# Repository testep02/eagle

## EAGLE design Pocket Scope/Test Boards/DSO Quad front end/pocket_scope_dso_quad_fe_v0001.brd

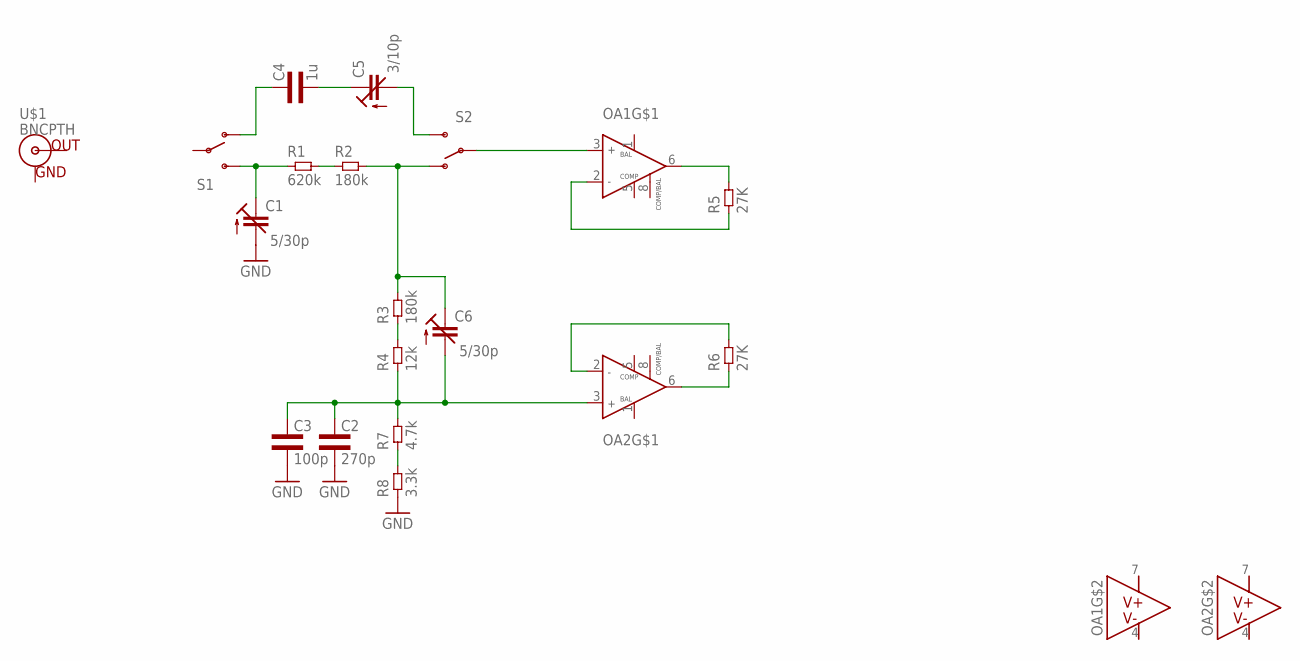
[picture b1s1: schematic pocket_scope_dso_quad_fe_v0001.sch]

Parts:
C1, C6: 5/30p; CTRIM3018_11
C2: 270p; 0603L3
C3: 100p; 0603L3
C4: 1u; 0603L3
C5: 3/10p; CTRIM3018_11
OA1, OA2: NE5534SOIC8; SOIC-8
R1: 620k; 0603L3
R2, R3: 180k; 0603L3
R4: 12k; 0603L3
R5, R6: 27K; 0603L3
R7: 4.7k; 0603L3
R8: 3.3k; 0603L3
S1, S2: SPARKFUN-ELECTROMECHANICAL_SWITCH-SPDTPTH_LOCK; SPARKFUN-ELECTROMECHANICAL_SWITCH-SPDT_LOCK.007S
U$1: BNCPTH; BNC

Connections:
GND: C1.- (A), C2.P$2 (2), C3.P$2 (2), R8.P$1 (1)
unnamed: C1.+ (E), R1.P$1 (1), S1.3 (S)
unnamed: R1.P$2 (2), R2.P$1 (1)
unnamed: C6.+ (E), R2.P$2 (2), R3.P$2 (2), S2.1 (O)
unnamed: OA1.3 (IN+), S2.2
unnamed: R3.P$1 (1), R4.P$2 (2)
unnamed: C2.P$1 (1), C3.P$1 (1), C6.- (A), OA2.3 (IN+), R4.P$1 (1), R7.P$2 (2)
unnamed: OA1.2 (IN-), R5.P$1 (1)
unnamed: OA2.2 (IN-), R6.P$2 (2)
unnamed: OA2.6 (OUT), R6.P$1 (1)
unnamed: OA1.6 (OUT), R5.P$2 (2)
unnamed: R7.P$1 (1), R8.P$2 (2)
unnamed: C5.- (A), S2.3 (S)
unnamed: C4.P$1 (1), S1.1 (O)
unnamed: C4.P$2 (2), C5.+ (E)
V+: OA1.7 (V+), OA2.7 (V+)
V-: OA1.4 (V-), OA2.4 (V-)

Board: 2 copper layers, 19 parts (0 on the bottom side), 17 nets, no tracks yet.

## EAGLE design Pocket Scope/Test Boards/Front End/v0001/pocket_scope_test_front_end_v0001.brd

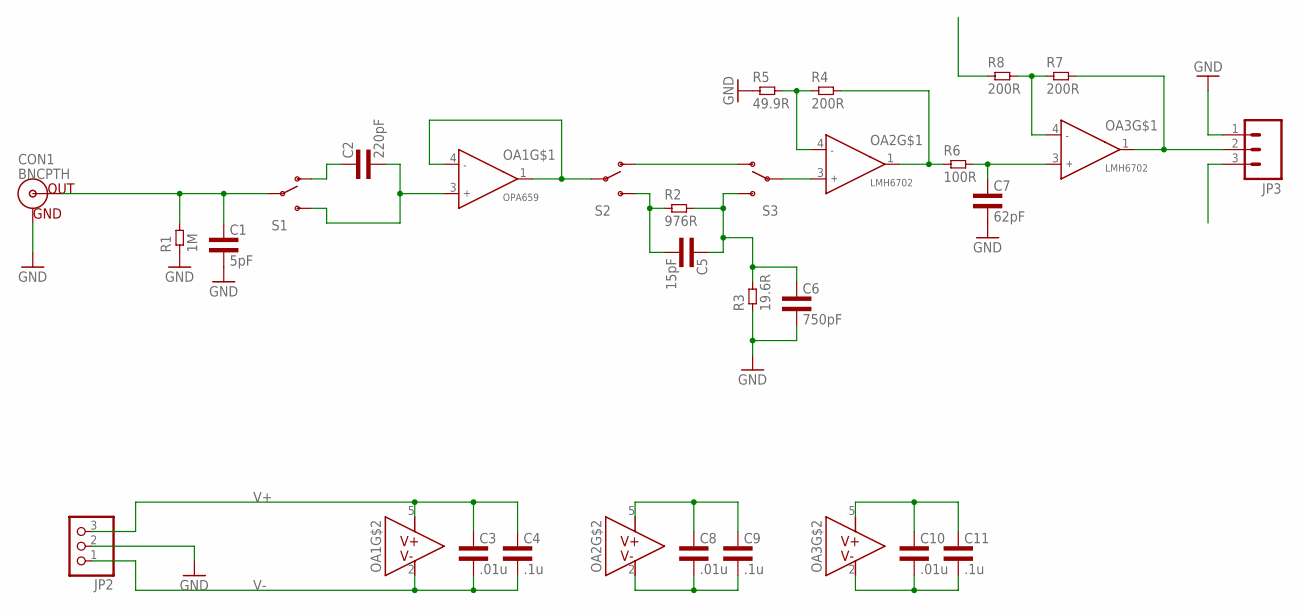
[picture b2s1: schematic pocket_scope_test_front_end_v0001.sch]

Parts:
C1: 5pF; 0805L3
C2: 220pF; 0805L3
C3, C8, C10: .01u; 0805L3
C4, C9, C11: .1u; 0805L3
C5: 15pF; 0805L3
C6: 750pF; 0805L3
C7: 62pF; 0805L3
CON1: BNCPTH; BNC
JP2: PINHD-1X3; 1X03
JP3: M03LOCK; 1X03_LOCK
OA1: OPA659; R-PDSO-G5
OA2, OA3: LMH6702; R-PDSO-G5
R1: 1M; 0805L3
R2: 976R; 0805L3
R3: 19.6R; 0805L3
R4, R7, R8: 200R; 0805L3
R5: 49.9R; 0805L3
R6: 100R; 0805L3
S1, S2, S3: SPARKFUN-ELECTROMECHANICAL_SWITCH-SPDTPTH_LOCK; SPARKFUN-ELECTROMECHANICAL_SWITCH-SPDT_LOCK.007S

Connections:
GND: C1.2, C6.2, C7.2, CON1.GND, JP2.2, JP3.1, R1.1, R3.1, R5.1
unnamed: C2.2, OA1.3 (INA+), S1.3 (S)
unnamed: C2.1, S1.1 (O)
unnamed: OA1.1 (OUTA), OA1.4 (INA-), S2.2
unnamed: C1.1, CON1.S (OUT), R1.2, S1.2
unnamed: C5.2, R2.1, S2.3 (S)
unnamed: C5.1, C6.1, R2.2, R3.2, S3.3 (S)
unnamed: S2.1 (O), S3.1 (O)
unnamed: OA2.3 (INA+), S3.2
unnamed: OA2.4 (INA-), R4.1, R5.2
unnamed: OA2.1 (OUTA), R4.2, R6.1
unnamed: C7.1, OA3.3 (INA+), R6.2
unnamed: JP3.2, OA3.1 (OUTA), R7.2
unnamed: OA3.4 (INA-), R7.1, R8.2
V+: C3.1, C4.1, C8.1, C9.1, C10.1, C11.1, JP2.3, OA1.5 (V+), OA2.5 (V+), OA3.5 (V+)
V-: C3.2, C4.2, C8.2, C9.2, C10.2, C11.2, JP2.1, OA1.2 (V-), OA2.2 (V-), OA3.2 (V-)
V_OS: JP3.3, R8.1

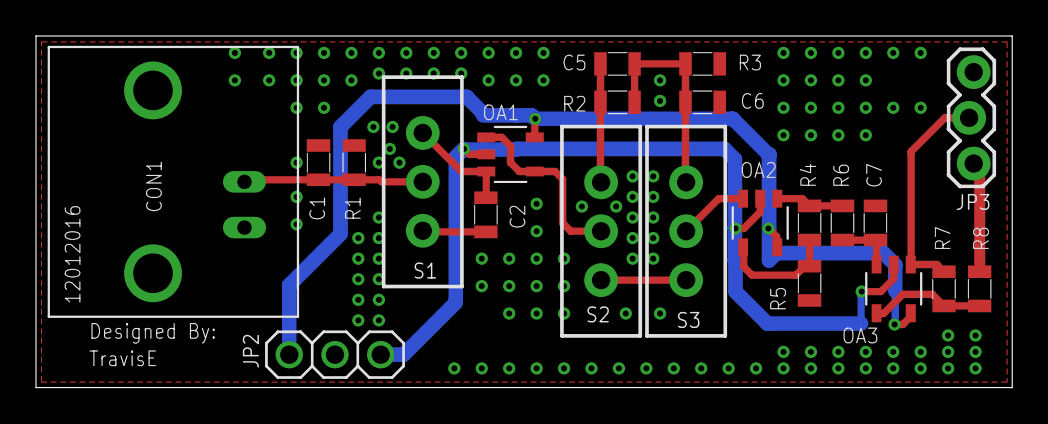
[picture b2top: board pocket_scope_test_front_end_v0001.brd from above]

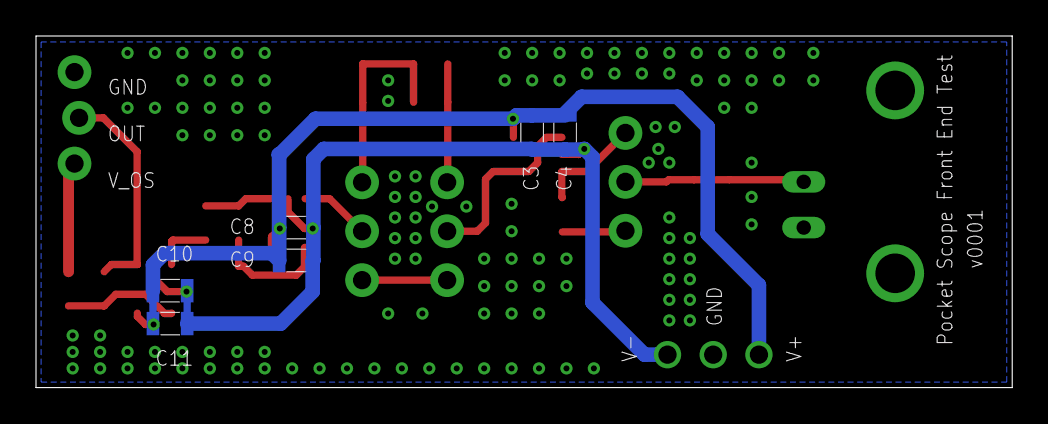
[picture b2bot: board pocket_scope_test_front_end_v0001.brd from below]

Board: 2 copper layers, 54.2 x 19.5 mm, 28 parts (6 on the bottom side), 17 nets.

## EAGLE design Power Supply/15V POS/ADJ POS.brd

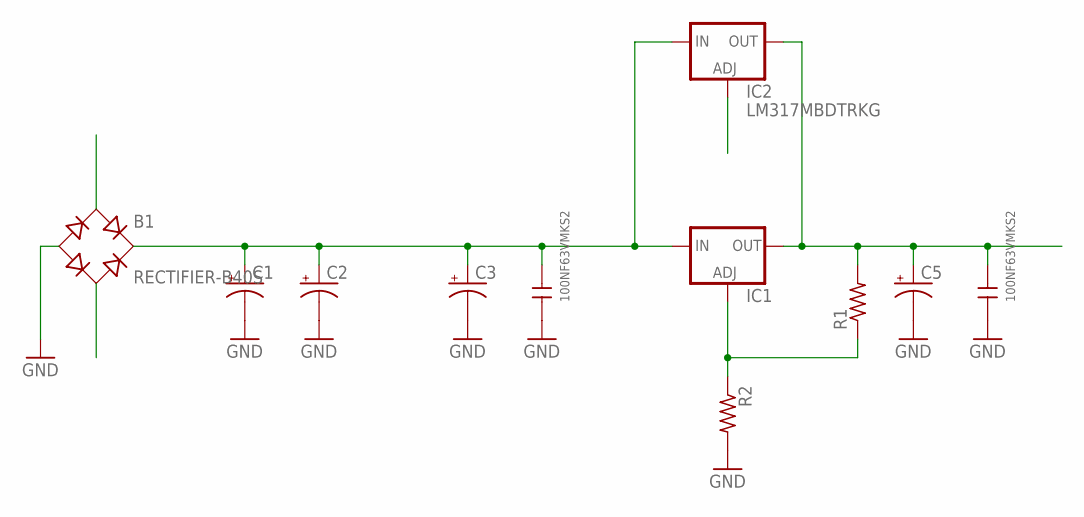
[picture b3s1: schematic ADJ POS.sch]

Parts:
B1: RECTIFIER-B40S; B40S
C1, C2: CPOL-USE7.5-16; E7,5-16
C3, C5: CPOL-USE2-5; E2-5
C4, C6: 100NF63VMKS2; 2,5X6,5RM5,0
IC1: LM317TS; 317TS
IC2: LM317MBDTRKG; DPACK
R1, R2: R-US_0309/12; 0309/12

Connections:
AC_1: B1.AC1
AC_2: B1.AC2
ADJ: IC1.1 (ADJ), IC2.1 (ADJ), R1.1, R2.1
GND: B1.-, C1.-, C2.-, C3.-, C4.1, C5.-, C6.1, R2.2
IN: B1.+, C1.+, C2.+, C3.+, C4.2, IC1.3 (IN), IC2.3 (IN)
OUT: C5.+, C6.2, IC1.2 (OUT), IC2.4 (OUT), R1.2

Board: 2 copper layers, 11 parts (0 on the bottom side), 4 nets, no tracks yet.

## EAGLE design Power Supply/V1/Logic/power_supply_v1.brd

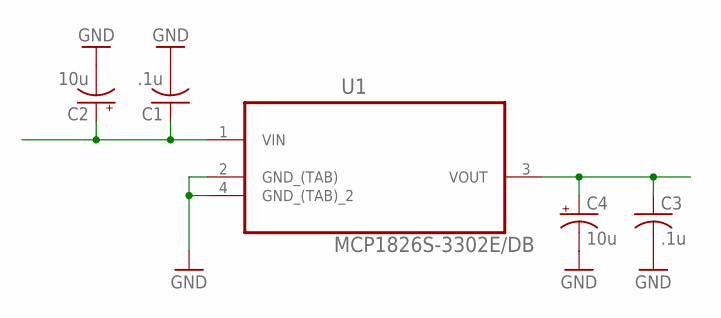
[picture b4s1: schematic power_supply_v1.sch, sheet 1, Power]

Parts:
C1, C3: .1u; C0603
C2, C4: 10u; D/7343-31W
U1: MCP1826S-3302E/DB; SOT230P700X180-4N

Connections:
3V3: C3.1, C4.+, U1.3 (VOUT)
GND: C1.2, C2.-, C3.2, C4.-, U1.2 (GND_(TAB)), U1.4 (GND_(TAB)_2)
unnamed: C1.1, C2.+, U1.1 (VIN)

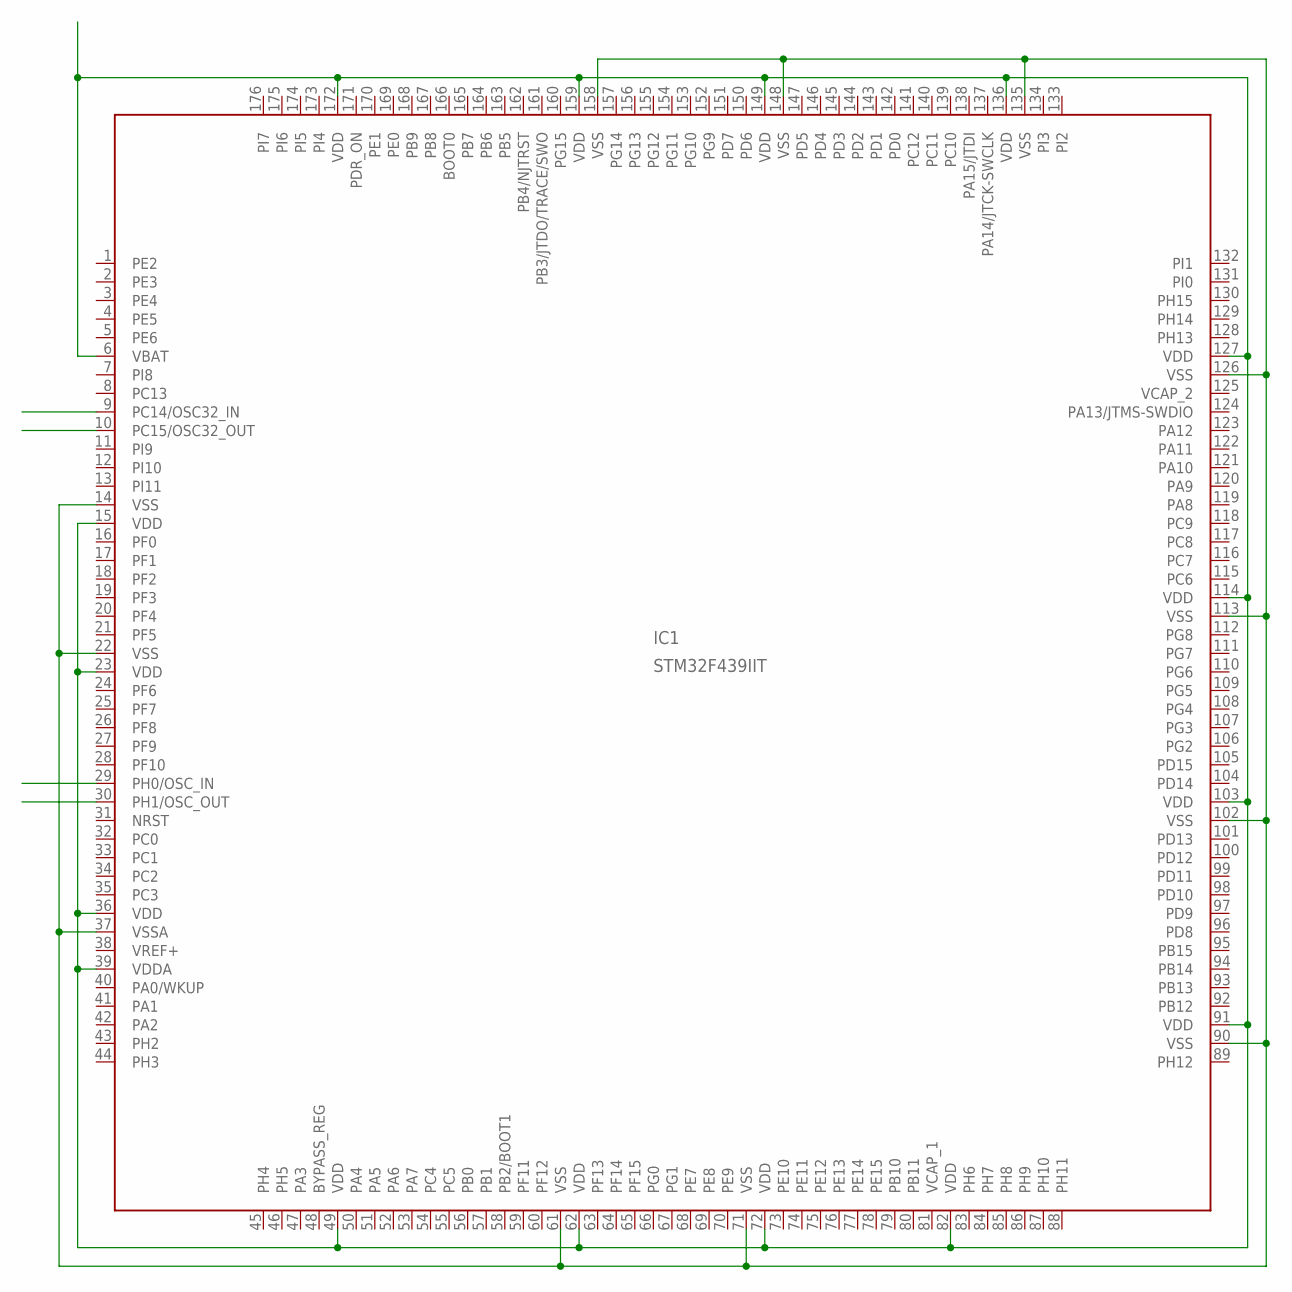
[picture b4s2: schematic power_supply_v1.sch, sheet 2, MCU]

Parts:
IC1: STM32F439IIT; LQFP-176

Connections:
unnamed: IC1.6 (VBAT), IC1.15 (VDD), IC1.23 (VDD), IC1.36 (VDD), IC1.39 (VDDA), IC1.49 (VDD), IC1.62 (VDD), IC1.72 (VDD), IC1.82 (VDD), IC1.91 (VDD), IC1.103 (VDD), IC1.114 (VDD), IC1.127 (VDD), IC1.136 (VDD), IC1.149 (VDD), IC1.159 (VDD), IC1.172 (VDD)
unnamed: IC1.14 (VSS), IC1.22 (VSS), IC1.37 (VSSA), IC1.61 (VSS), IC1.71 (VSS), IC1.90 (VSS), IC1.102 (VSS), IC1.113 (VSS), IC1.126 (VSS), IC1.135 (VSS), IC1.148 (VSS), IC1.158 (VSS)
PDR_ON: IC1.171 (PDR_ON)
VCAP_1: IC1.81 (VCAP_1)
VCAP_2: IC1.125 (VCAP_2)
VREF+: IC1.38 (VREF+)

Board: 2 copper layers, 6 parts (0 on the bottom side), 5 nets, no tracks yet.

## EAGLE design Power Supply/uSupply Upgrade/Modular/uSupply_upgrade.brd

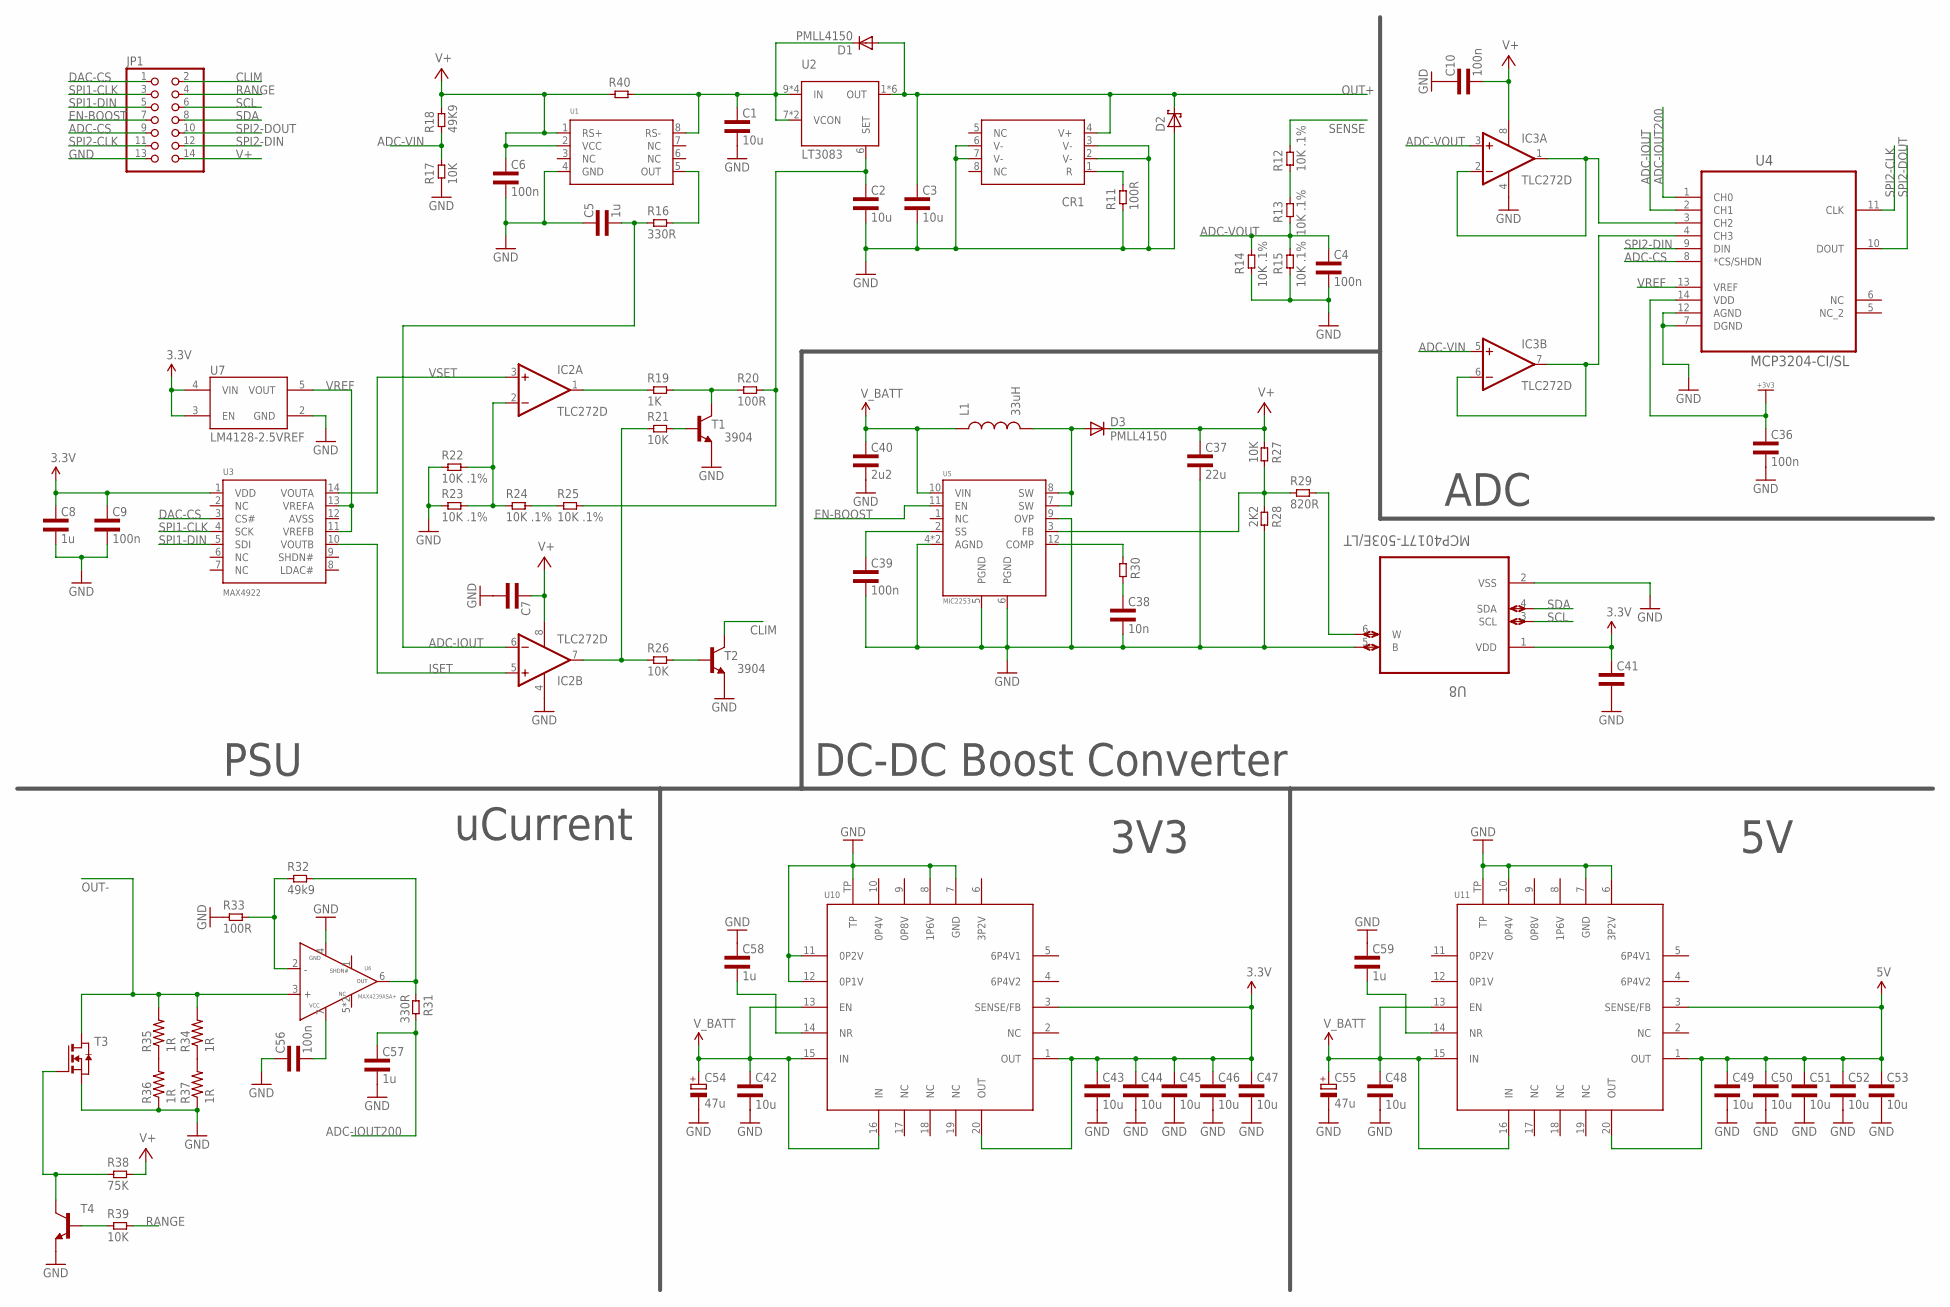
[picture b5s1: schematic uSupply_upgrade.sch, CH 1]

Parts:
C1, C2, C3, C42, C43, C44, C45, C46, C47, C48, C49, C50, C51, C52, C53: 10u; 0805L3
C4, C6, C9, C10, C36, C39, C56: 100n; 0603L3
C5, C8, C57, C58, C59: 1u; 0603L3
C7, C41: CAP0603L3; 0603L3
C37: 22u; 1206L3
C38: 10n; 0603L3
C40: 2u2; 0603L3
C54, C55: 47u; CT7343
CR1: LM334; R-PDSO-G8
D1, D3: PMLL4150; SOD80C
D2: SCHOTTKY-DIODESMD; SMB
IC2, IC3: TLC272D; SO08
JP1: PINHD-2X7; 2X07
L1: 33uH; SRN6045
R11, R20, R33: 100R; 0603L3
R12, R13, R14, R15, R22, R23, R24, R25: 10K .1%; 0603L3
R16, R31: 330R; 0603L3
R17, R21, R26, R27, R39: 10K; 0603L3
R18: 49K9; 0603L3
R19: 1K; 0603L3
R28: 2K2; 0603L3
R29: 820R; 0603L3
R30: RES0603L3; 0603L3
R32: 49k9; 0603L3
R34, R35, R36, R37: 1R; R2512
R38: 75K; 0603L3
R40: RES4527L3; 4527L3
T1, T2: 3904; SOT23-BEC
T3: NMOSSOT23; SOT-23
T4: MMBT3904LT1-NPN-SOT23-BEC; SOT23-BEC
U1: MAX4080; UMAX
U2: LT3083; DFN4X4
U3: MCP4922; TSSOP-14
U4: MCP3204-CI/SL; SOIC127P600X175-14N
U5: MIC2253; MLF3X3
U6: MAX4239; SOIC-8
U7: LM4128-2.5VREF; SOT23-5
U8: MCP4017T-503E/LT; SOT65P210X110-6N
U10, U11: POWER-SUPPLY_POS_V1_TI_LDO_TPS7A4700; POWER-SUPPLY_POS_V1_TI_LDO_VQFN-20

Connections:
3.3V: C8.P$1 (1), C9.P$1 (1), C41.P$1 (1), C43.1, C44.1, C45.1, C46.1, C47.1, U3.1 (VDD), U7.3 (EN), U7.4 (VIN), U8.1 (VDD), U10.1 (OUT), U10.3 (SENSE/FB), U10.20 (OUT)
5V: C49.1, C50.1, C51.1, C52.1, C53.1, U11.1 (OUT), U11.3 (SENSE/FB), U11.20 (OUT)
+3V3: C36.P$1 (1), U4.14 (VDD)
ADC-CS: JP1.9, U4.8 (*CS/SHDN)
ADC-IOUT: C5.P$2 (2), IC2.6 (-IN), R16.P$1 (1), U4.2 (CH1)
ADC-IOUT200: C57.P$1 (1), R31.P$2 (2), U4.1 (CH0)
ADC-VIN: IC3.5 (+IN), R17.P$2 (2), R18.P$1 (1)
ADC-VOUT: C4.P$1 (1), IC3.3 (+IN), R13.P$1 (1), R14.P$2 (2), R15.P$2 (2)
CLIM: JP1.2, T2.C
DAC-CS: JP1.1, U3.3 (CS#)
EN-BOOST: JP1.7, U5.11 (EN)
GND: C1.2, C2.2, C3.2, C4.P$2 (2), C5.P$1 (1), C6.P$2 (2), C7.P$2 (2), C8.P$2 (2), C9.P$2 (2), C10.P$1 (1), C36.P$2 (2), C37.2, C38.P$2 (2), C39.P$2 (2), C40.P$2 (2), C41.P$2 (2), C42.2, C43.2, C44.2, C45.2, C46.2, C47.2, C48.2, C49.2, C50.2, C51.2, C52.2, C53.2, C54.-, C55.-, C56.P$1 (1), C57.P$2 (2), C58.P$1 (1), C59.P$1 (1), CR1.2 (V-), CR1.3 (V-), CR1.6 (V-), CR1.7 (V-), D2.A, IC2.4 (V-), IC3.4 (V-), JP1.13, R11.P$1 (1), R14.P$1 (1), R15.P$1 (1), R17.P$1 (1), R22.P$1 (1), R23.P$1 (1), R28.P$2 (2), R33.P$1 (1), R36.1, R37.1, T1.E, T2.E, T3.2 (S), T4.E, U1.4 (GND), U4.7 (DGND), U4.12 (AGND), U5.4 (AGND), U5.5 (PGND), U5.6 (PGND), U5.9 (OVP), U5.TP (AGND), U6.4 (GND), U7.2 (GND), U8.2 (VSS), U8.5 (B), U10.7 (GND), U10.8 (1P6V), U10.11 (0P2V), U10.12 (0P1V), U10.TP, U11.6 (3P2V), U11.7 (GND), U11.10 (0P4V), U11.TP
ISET: IC2.5 (+IN), U3.10 (VOUTB)
I_R: CR1.1 (R), R11.P$2 (2)
unnamed: IC3.1 (OUT), IC3.2 (-IN), U4.3 (CH2)
unnamed: C56.P$2 (2), U6.7 (VCC)
unnamed: D3.A, L1.2, U5.7 (SW), U5.8 (SW)
unnamed: C59.P$2 (2), U11.14 (NR)
unnamed: R16.P$2 (2), U1.5 (OUT)
unnamed: C58.P$2 (2), U10.14 (NR)
unnamed: R31.P$1 (1), R32.P$2 (2), U6.6 (OUT)
unnamed: IC3.6 (-IN), IC3.7 (OUT), U4.4 (CH3)
unnamed: R29.P$2 (2), U8.6 (W)
unnamed: R12.P$1 (1), R13.P$2 (2)
unnamed: R27.P$2 (2), R28.P$1 (1), R29.P$1 (1), U5.3 (FB)
unnamed: R30.P$1 (1), U5.12 (COMP)
unnamed: C38.P$1 (1), R30.P$2 (2)
unnamed: IC2.1 (OUT), R19.P$1 (1)
unnamed: R19.P$2 (2), R20.P$1 (1), T1.C
unnamed: R21.P$2 (2), T1.B
unnamed: IC2.2 (-IN), R22.P$2 (2), R23.P$2 (2), R24.P$1 (1)
unnamed: R24.P$2 (2), R25.P$1 (1)
unnamed: R32.P$1 (1), R33.P$2 (2), U6.2 (-)
unnamed: C39.P$1 (1), U5.2 (SS)
unnamed: IC2.7 (OUT), R21.P$1 (1), R26.P$1 (1)
unnamed: R26.P$2 (2), T2.B
unnamed: R34.1, R37.2
unnamed: R35.1, R36.2
unnamed: R38.P$1 (1), T3.3 (G), T4.C
unnamed: R39.P$1 (1), T4.B
OUT+: C3.1, CR1.4 (V+), D1.A, D2.C, U2.1 (OUT), U2.2 (OUT), U2.3 (OUT), U2.4 (OUT), U2.5 (OUT), U2.TP (OUT)
OUT-: R34.2, R35.2, T3.1 (D), U6.3 (+)
RANGE: JP1.4, R39.P$2 (2)
SCL: JP1.6, U8.3 (SCL)
SDA: JP1.8, U8.4 (SDA)
SENSE: R12.P$2 (2)
SET: C2.1, R20.P$2 (2), R25.P$2 (2), U2.6 (SET)
SPI1-CLK: JP1.3, U3.4 (SCK)
SPI1-DIN: JP1.5, U3.5 (SDI)
SPI2-CLK: JP1.11, U4.11 (CLK)
SPI2-DIN: JP1.12, U4.9 (DIN)
SPI2-DOUT: JP1.10, U4.10 (DOUT)
V+: C6.P$1 (1), C7.P$1 (1), C10.P$2 (2), C37.1, D3.C, IC2.8 (V+), IC3.8 (V+), JP1.14, R18.P$2 (2), R27.P$1 (1), R38.P$2 (2), R40.1, U1.1 (RS+), U1.2 (VCC)
V+_REG: C1.1, D1.C, R40.2, U1.8 (RS-), U2.7 (VCON), U2.8 (VCON), U2.9 (IN), U2.10 (IN), U2.11 (IN), U2.12 (IN)
VREF: U3.11 (VREFB), U3.13 (VREFA), U4.13 (VREF), U7.5 (VOUT)
VSET: IC2.3 (+IN), U3.14 (VOUTA)
V_BATT: C40.P$1 (1), C42.1, C48.1, C54.+, C55.+, L1.1, U5.10 (VIN), U10.13 (EN), U10.15 (IN), U10.16 (IN), U11.13 (EN), U11.15 (IN), U11.16 (IN)

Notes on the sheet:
PSU
ADC
DC-DC Boost Converter
3V3
uCurrent

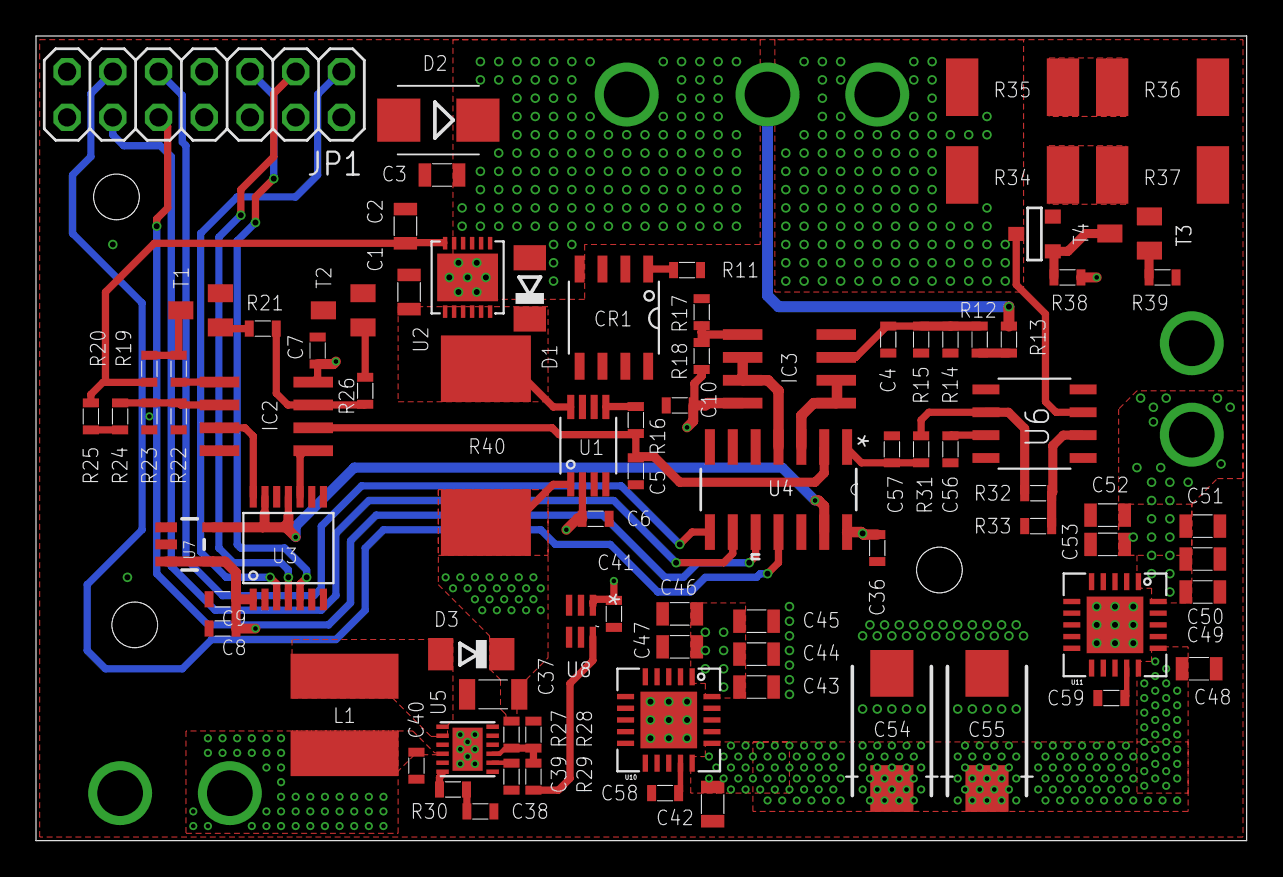
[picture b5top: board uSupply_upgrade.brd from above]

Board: 4 copper layers, 67.3 x 44.7 mm, 86 parts (0 on the bottom side), 56 nets.

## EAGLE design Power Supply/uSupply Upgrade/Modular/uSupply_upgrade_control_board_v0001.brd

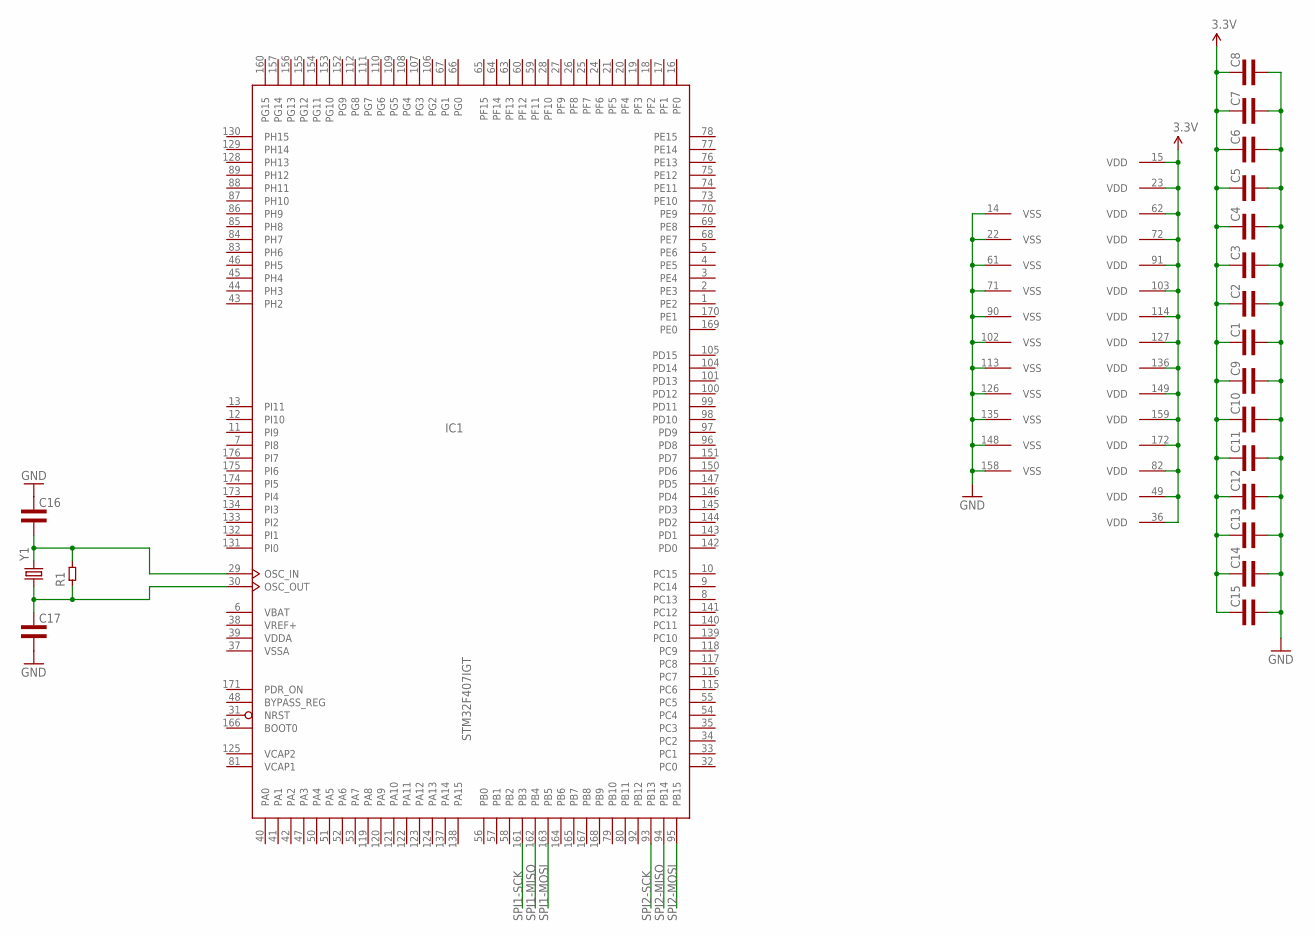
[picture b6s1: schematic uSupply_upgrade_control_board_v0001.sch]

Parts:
C1, C2, C3, C4, C5, C6, C7, C8, C9, C10, C11, C12, C13, C14, C15, C16, C17: CAP0402L3; 0402L3
IC1: STM32F407IGT; LQFP176
R1: RES0402L3; 0402L3
Y1: CRYSTALHC49US; HC49US

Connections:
3.3V: C1.P$1 (1), C2.P$1 (1), C3.P$1 (1), C4.P$1 (1), C5.P$1 (1), C6.P$1 (1), C7.P$1 (1), C8.P$1 (1), C9.P$1 (1), C10.P$1 (1), C11.P$1 (1), C12.P$1 (1), C13.P$1 (1), C14.P$1 (1), C15.P$1 (1), IC1.15 (VDD), IC1.23 (VDD), IC1.36 (VDD), IC1.49 (VDD), IC1.62 (VDD), IC1.72 (VDD), IC1.82 (VDD), IC1.91 (VDD), IC1.103 (VDD), IC1.114 (VDD), IC1.127 (VDD), IC1.136 (VDD), IC1.149 (VDD), IC1.159 (VDD), IC1.172 (VDD)
GND: C1.P$2 (2), C2.P$2 (2), C3.P$2 (2), C4.P$2 (2), C5.P$2 (2), C6.P$2 (2), C7.P$2 (2), C8.P$2 (2), C9.P$2 (2), C10.P$2 (2), C11.P$2 (2), C12.P$2 (2), C13.P$2 (2), C14.P$2 (2), C15.P$2 (2), C16.P$1 (1), C17.P$2 (2), IC1.14 (VSS), IC1.22 (VSS), IC1.61 (VSS), IC1.71 (VSS), IC1.90 (VSS), IC1.102 (VSS), IC1.113 (VSS), IC1.126 (VSS), IC1.135 (VSS), IC1.148 (VSS), IC1.158 (VSS)
unnamed: C16.P$2 (2), IC1.29 (OSC_IN), R1.P$2 (2), Y1.2
unnamed: C17.P$1 (1), IC1.30 (OSC_OUT), R1.P$1 (1), Y1.1
SPI1-MISO: IC1.162 (PB4)
SPI1-MOSI: IC1.163 (PB5)
SPI1-SCK: IC1.161 (PB3)
SPI2-MISO: IC1.94 (PB14)
SPI2-MOSI: IC1.95 (PB15)
SPI2-SCK: IC1.93 (PB13)
VBAT: IC1.6 (VBAT)
VCAP1: IC1.81 (VCAP1)
VCAP2: IC1.125 (VCAP2)
VDDA: IC1.39 (VDDA)
VREF+: IC1.38 (VREF+)
VSSA: IC1.37 (VSSA)

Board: 2 copper layers, 20 parts (0 on the bottom side), 4 nets, no tracks yet.

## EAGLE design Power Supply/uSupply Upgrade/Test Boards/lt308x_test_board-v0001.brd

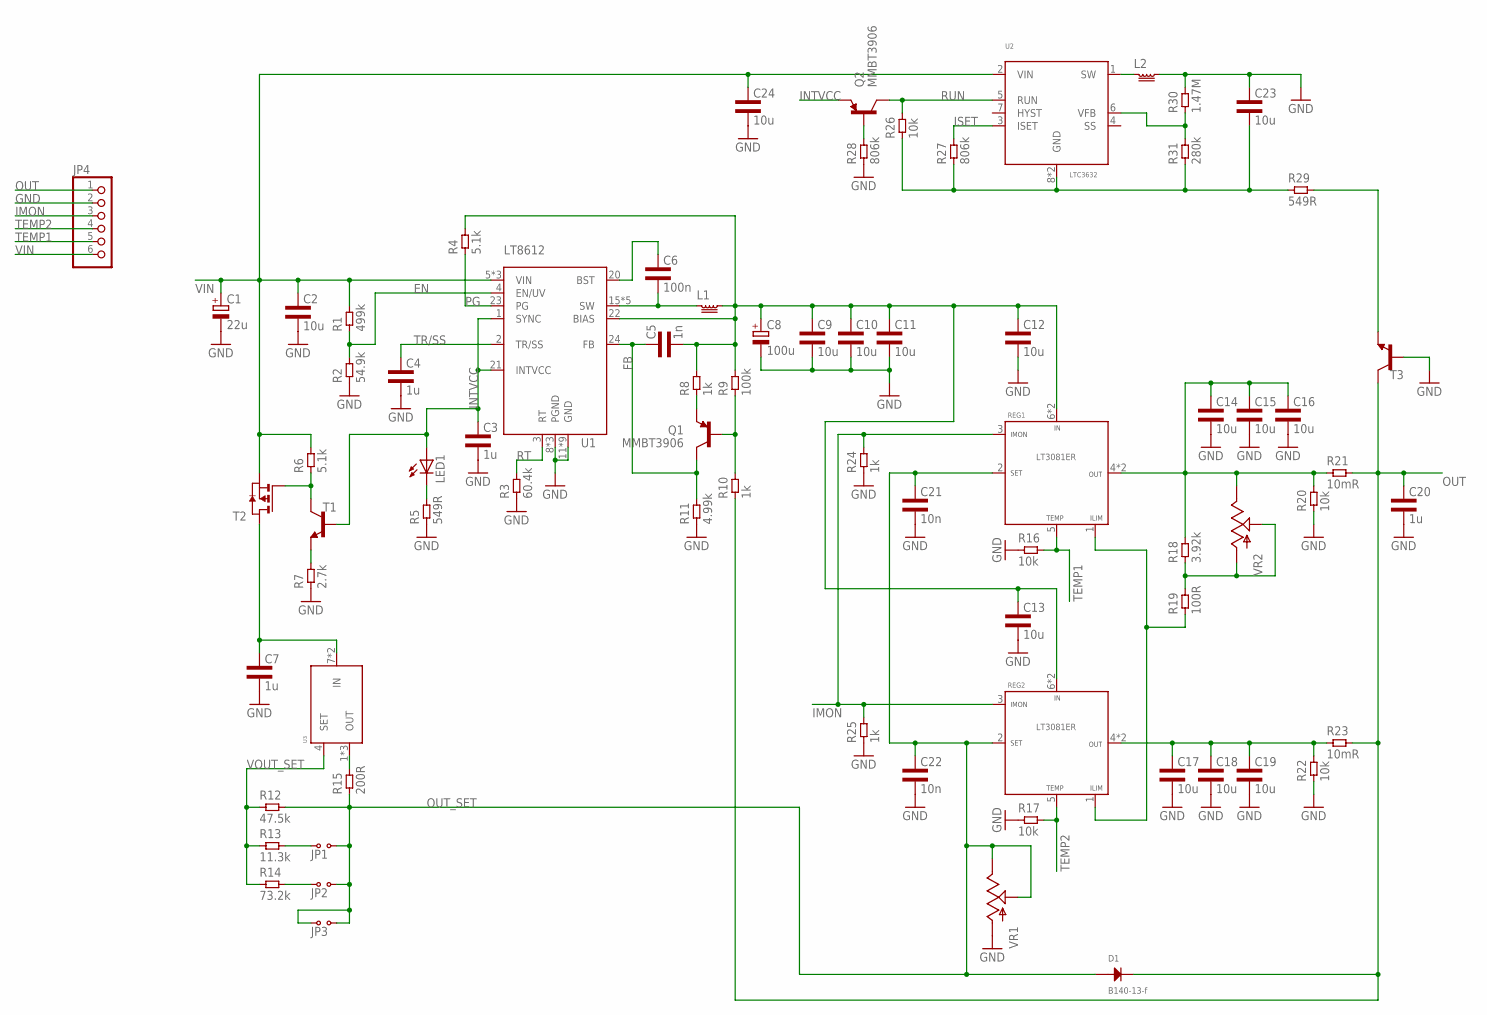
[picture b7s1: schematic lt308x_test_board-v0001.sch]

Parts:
C1: 22u; UD-6,3X7,7_NICHICON
C2, C9, C10, C11, C12, C13, C14, C15, C16, C17, C18, C19: 10u; 1210L3
C3, C4: 1u; 0603L3
C5: 1n; 0603L3
C6: 100n; 0603L3
C7: 1u; 0805L3
C8: 100u; UD-6,3X7,7_NICHICON
C20: 1u; 1206L3
C21, C22: 10n; 0603L3
C23, C24: 10u; 0805L3
D1: B140-13-f; SMA-2
JP1, JP2, JP3: JUMPER2
JP4: PINHD-1X6; 1X06
L1: INDUCTOR10.5X10.5; 10.5X10.5
L2: INDUCTOR1210L1; 1210L1
LED1: LEDCHIPLED_0805; CHIPLED_0805
Q1, Q2: MMBT3906; SOT23
R1: 499k; 0603L3
R2: 54.9k; 0603L3
R3: 60.4k; 0603L3
R4, R6: 5.1k; 0603L3
R5, R29: 549R; 0603L3
R7: 2.7k; 0603L3
R8, R10, R24, R25: 1k; 0603L3
R9: 100k; 0603L3
R11: 4.99k; 0603L3
R12: 47.5k; 0603L3
R13: 11.3k; 0603L3
R14: 73.2k; 0603L3
R15: 200R; 0805L3
R16, R17, R26: 10k; 0603L3
R18: 3.92k; 0603L3
R19: 100R; 0603L3
R20, R22: 10k; 1210L3
R21, R23: 10mR; 1210L3
R27, R28: 806k; 0603L3
R30: 1.47M; 0603L3
R31: 280k; 0603L3
REG1, REG2: LT3081ER; DPAK-7
T1, T3: TRANSISTOR_MMBT3904LT1-NPN-SOT23-BEC; TRANSISTOR_SOT23-BEC
T2: PMOSSOT23; SOT-23
U1: LT8612; UDE-3X6
U2: LTC3632; DFN-3X3
U3: LT3092; DD-8
VR1, VR2: POT; ALPS_POT

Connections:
-5V: C23.2, R26.P$1 (1), R27.P$1 (1), R29.P$1 (1), R31.P$1 (1), U2.8 (GND), U2.TP (GND)
EN: R1.P$1 (1), R2.P$2 (2), U1.4 (EN/UV)
FB: C5.P$1 (1), Q1.3 (C), R11.P$2 (2), U1.24 (FB)
FB_NEG: R30.P$1 (1), R31.P$2 (2), U2.6 (VFB)
GND: C1.-, C2.P$2 (2), C3.P$2 (2), C4.P$2 (2), C7.2, C8.-, C9.P$2 (2), C10.P$2 (2), C11.P$2 (2), C12.P$2 (2), C13.P$2 (2), C14.P$2 (2), C15.P$2 (2), C16.P$2 (2), C17.P$2 (2), C18.P$2 (2), C19.P$2 (2), C20.2, C21.P$2 (2), C22.P$2 (2), C23.1, C24.2, JP4.2, L2.2, R2.P$1 (1), R3.P$1 (1), R5.P$1 (1), R7.P$1 (1), R11.P$1 (1), R16.P$1 (1), R17.P$1 (1), R20.P$1 (1), R22.P$1 (1), R24.P$1 (1), R25.P$1 (1), R28.P$1 (1), R30.P$2 (2), T3.B, U1.8 (PGND), U1.9 (PGND), U1.10 (PGND), U1.11 (GND), U1.12 (GND), U1.13 (GND), U1.14 (GND), U1.25 (GND), U1.26 (GND), U1.27 (GND), U1.28 (GND), U1.TP (GND), VR1.P$3 (A)
ILIM: R19.P$1 (1), REG1.1 (ILIM), REG2.1 (ILIM)
IMON: JP4.3, R24.P$2 (2), R25.P$2 (2), REG1.3 (IMON), REG2.3 (IMON)
INTVCC: C3.P$1 (1), LED1.A, Q2.2 (E), T1.B, U1.1 (SYNC), U1.21 (INTVCC)
ISET: R27.P$2 (2), U2.3 (ISET)
LED: LED1.C, R5.P$2 (2)
unnamed: C7.1, T2.1 (D), U3.7 (IN), U3.8 (IN)
unnamed: R15.2, U3.1 (OUT), U3.2 (OUT), U3.9 (OUT)
unnamed: C6.P$1 (1), U1.20 (BST)
unnamed: JP1.1, R13.P$2 (2)
unnamed: JP2.1, R14.P$2 (2)
unnamed: C5.P$2 (2), C8.+, C9.P$1 (1), C10.P$1 (1), C11.P$1 (1), C12.P$1 (1), C13.P$1 (1), L1.2, R4.P$2 (2), R8.P$2 (2), R9.P$2 (2), REG1.6 (IN), REG1.7 (IN), REG2.6 (IN), REG2.7 (IN), U1.22 (BIAS)
unnamed: Q1.2 (E), R8.P$1 (1)
unnamed: R6.P$1 (1), T1.C, T2.3 (G)
unnamed: R7.P$2 (2), T1.E
unnamed: R18.P$1 (1), R19.P$2 (2), VR2.P$2 (S), VR2.P$3 (A)
unnamed: C14.P$1 (1), C15.P$1 (1), C16.P$1 (1), R18.P$2 (2), R20.P$2 (2), R21.P$1 (1), REG1.4 (OUT), REG1.TAB (OUT), VR2.P$1 (E)
unnamed: R29.P$2 (2), T3.E
unnamed: C17.P$1 (1), C18.P$1 (1), C19.P$1 (1), R22.P$2 (2), R23.P$1 (1), REG2.4 (OUT), REG2.TAB (OUT)
OUT: C20.1, D1.2 (CATHODE), JP4.1, R10.P$1 (1), R21.P$2 (2), R23.P$2 (2), T3.C
OUT_SET: C21.P$1 (1), C22.P$1 (1), D1.1 (ANODE), JP1.2, JP2.2, JP3.1, JP3.2, R12.P$2 (2), R15.1, REG1.2 (SET), REG2.2 (SET), VR1.P$1 (E), VR1.P$2 (S)
PG: R4.P$1 (1), U1.23 (PG)
Q1_GATE: Q1.1 (B), R9.P$1 (1), R10.P$2 (2)
Q2_GATE: Q2.1 (B), R28.P$2 (2)
RT: R3.P$2 (2), U1.3 (RT)
RUN: Q2.3 (C), R26.P$2 (2), U2.5 (RUN)
SW_BOOST: C6.P$2 (2), L1.1, U1.15 (SW), U1.16 (SW), U1.17 (SW), U1.18 (SW), U1.19 (SW)
SW_NEG: L2.1, U2.1 (SW)
TEMP1: JP4.5, R16.P$2 (2), REG1.5 (TEMP)
TEMP2: JP4.4, R17.P$2 (2), REG2.5 (TEMP)
TR/SS: C4.P$1 (1), U1.2 (TR/SS)
VIN: C1.+, C2.P$1 (1), C24.1, JP4.6, R1.P$2 (2), R6.P$2 (2), T2.2 (S), U1.5 (VIN), U1.6 (VIN), U1.7 (VIN), U2.2 (VIN)
VOUT_SET: R12.P$1 (1), R13.P$1 (1), R14.P$1 (1), U3.4 (SET)

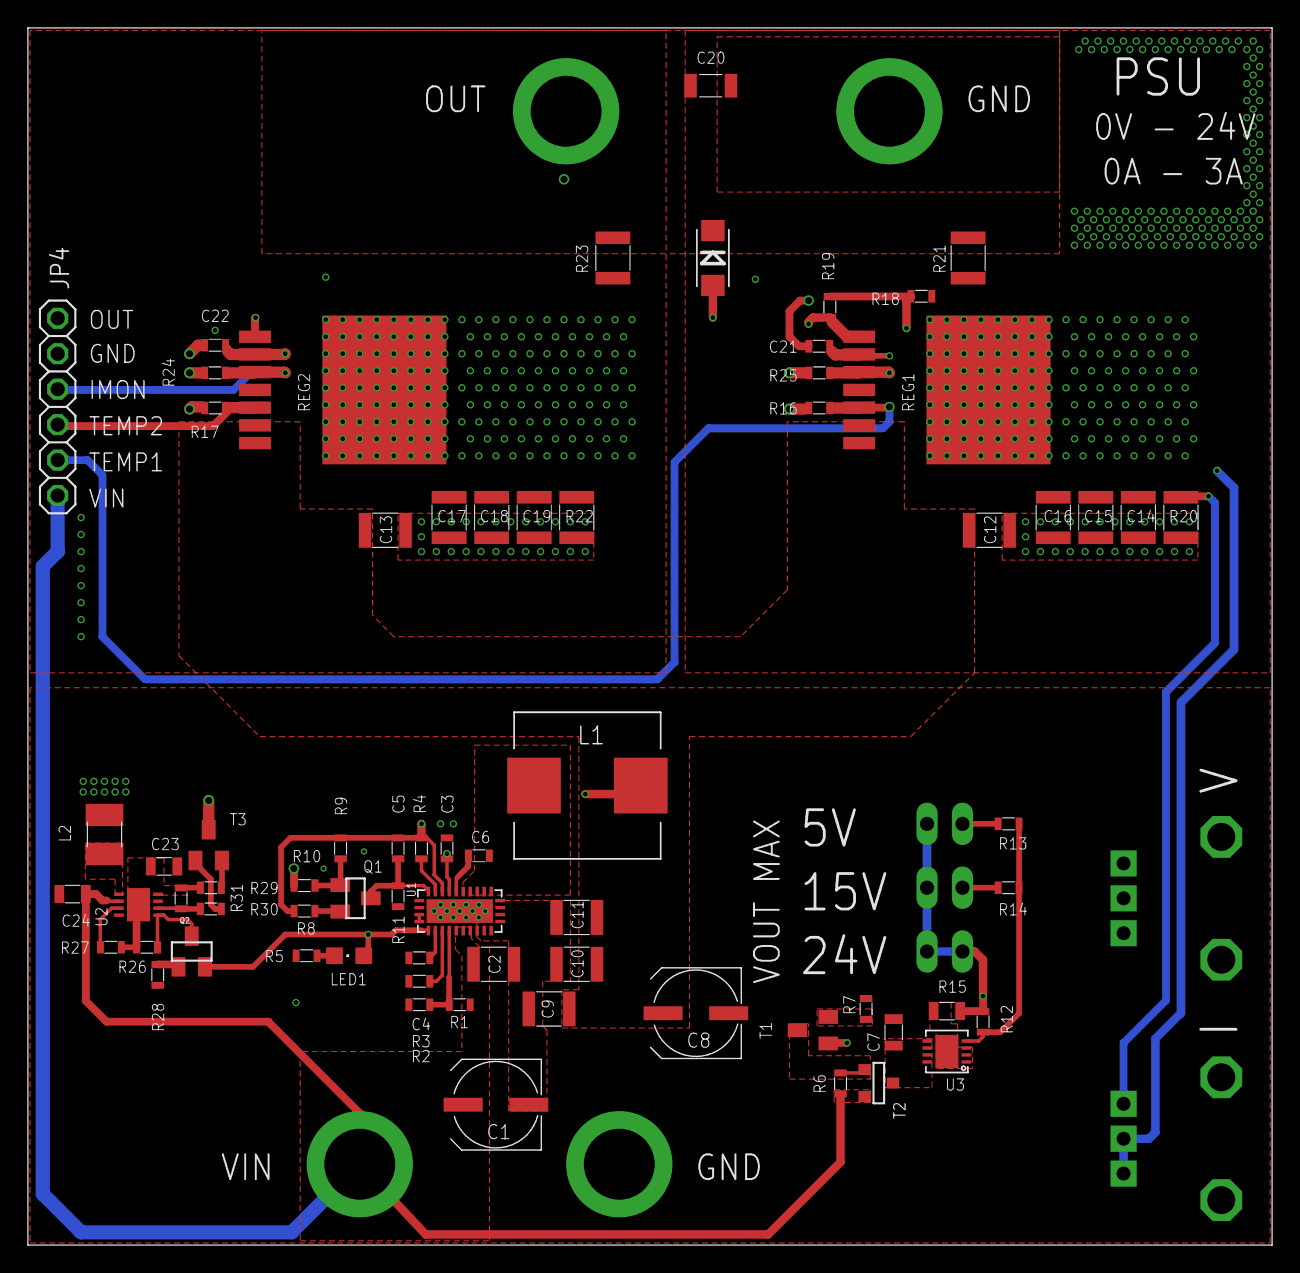
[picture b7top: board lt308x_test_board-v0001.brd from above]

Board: 4 copper layers, 89.1 x 87.2 mm, 75 parts (0 on the bottom side), 37 nets.

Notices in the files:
parts and their libraries:
SparkFun-Connectors: Licensing: CC v3.0 Share-Alike You are welcome to use this library for commercial purposes.
